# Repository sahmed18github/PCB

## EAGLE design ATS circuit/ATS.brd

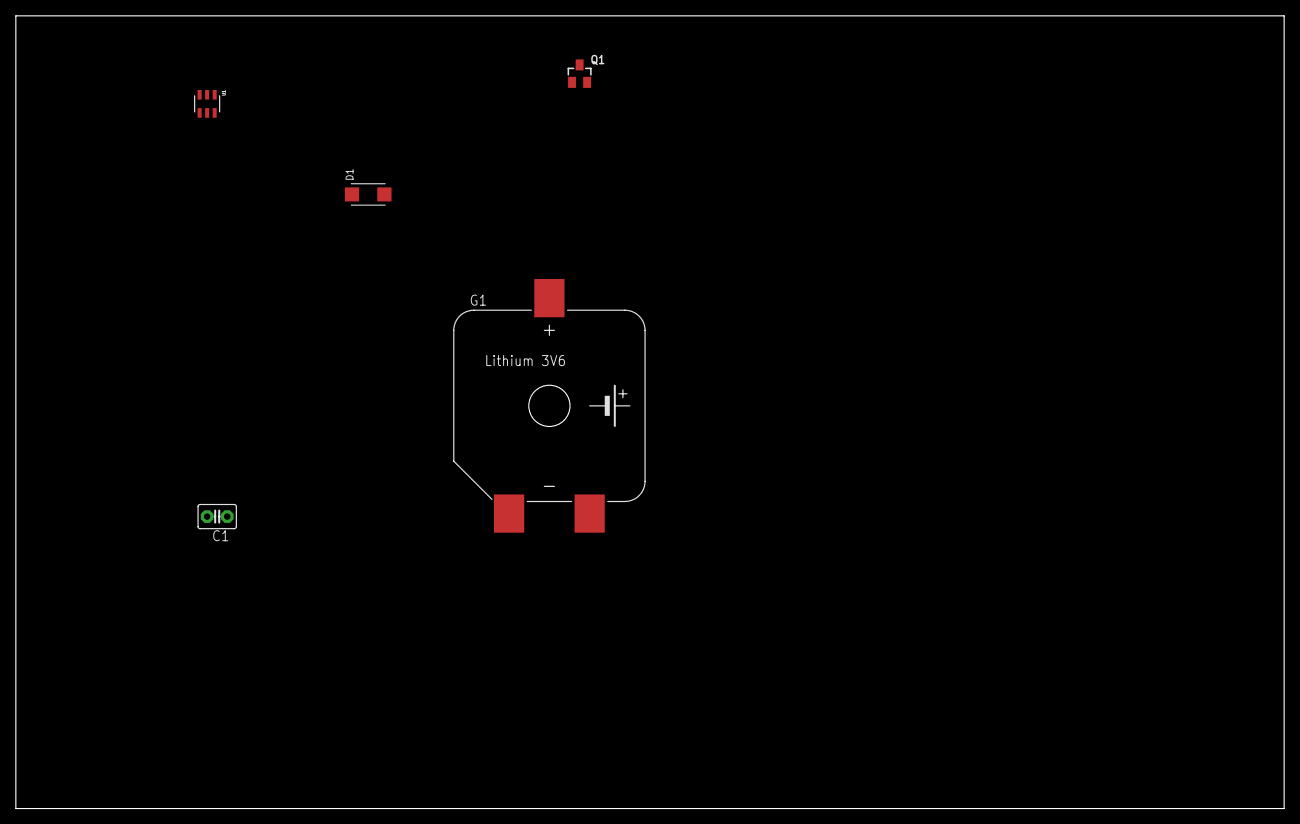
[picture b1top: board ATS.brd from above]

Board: 2 copper layers, 160.0 x 100.0 mm, 5 parts (0 on the bottom side), 4 nets, no tracks yet.

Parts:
C1: 22uF; C2.5-3
D1: SMD-DIODE-SCHOTTKY-40V-1A(DO-214AC); DO-214AC
G1: SL-340/SM3.6V
Q1: FDN306P; SSOT-3
U1: LTC4412ES6; TSOT-23_S6

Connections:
GND: C1.2, G1.-, U1.2, U1.3
unnamed: Q1.1, U1.5
unnamed: G1.+, Q1.2, U1.1
VCC: C1.1, D1.1, D1.2, Q1.3, U1.4, U1.6

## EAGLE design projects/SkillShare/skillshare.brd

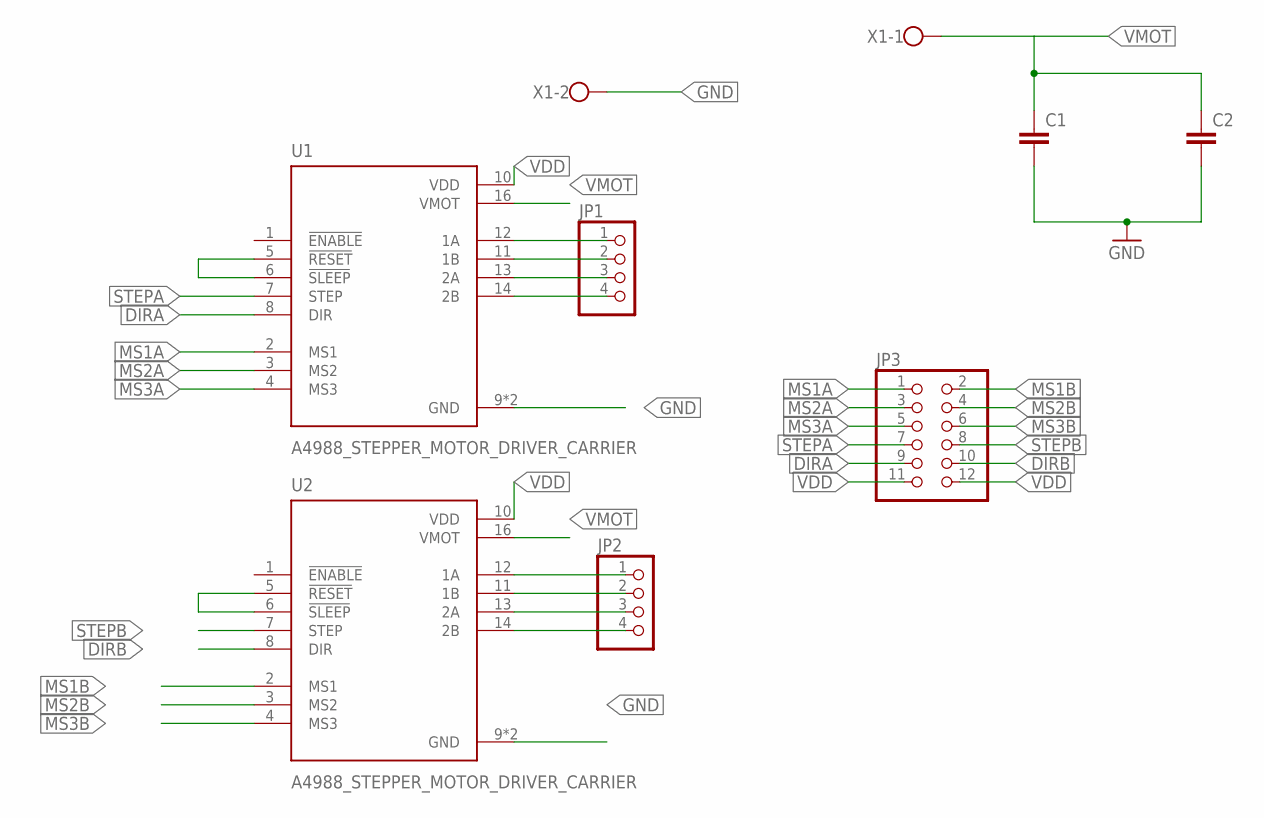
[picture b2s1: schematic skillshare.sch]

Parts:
C1, C2: C-EU025-025X050; C025-025X050
JP1, JP2: PINHD-1X4; 1X04
JP3: PINHD-2X6; 2X06
U1, U2: A4988_STEPPER_MOTOR_DRIVER_CARRIER; MODULE_A4988_STEPPER_MOTOR_DRIVER_CARRIER
X1: W237-102

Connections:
DIRA: JP3.9, U1.8 (DIR)
DIRB: JP3.10, U2.8 (DIR)
GND: C1.2, C2.2, U1.9 (GND), U1.15 (GND), U2.9 (GND), U2.15 (GND), X1.2
MS1A: JP3.1, U1.2 (MS1)
MS1B: JP3.2, U2.2 (MS1)
MS2A: JP3.3, U1.3 (MS2)
MS2B: JP3.4, U2.3 (MS2)
MS3A: JP3.5, U1.4 (MS3)
MS3B: JP3.6, U2.4 (MS3)
unnamed: JP1.1, U1.12 (1A)
unnamed: JP1.2, U1.11 (1B)
unnamed: JP1.3, U1.13 (2A)
unnamed: JP1.4, U1.14 (2B)
unnamed: JP2.1, U2.12 (1A)
unnamed: JP2.2, U2.11 (1B)
unnamed: JP2.3, U2.13 (2A)
unnamed: JP2.4, U2.14 (2B)
unnamed: U2.5 (!RESET), U2.6 (!SLEEP)
unnamed: U1.5 (!RESET), U1.6 (!SLEEP)
STEPA: JP3.7, U1.7 (STEP)
STEPB: JP3.8, U2.7 (STEP)
VDD: JP3.11, JP3.12, U1.10 (VDD), U2.10 (VDD)
VMOT: C1.1, C2.1, U1.16 (VMOT), U2.16 (VMOT), X1.1

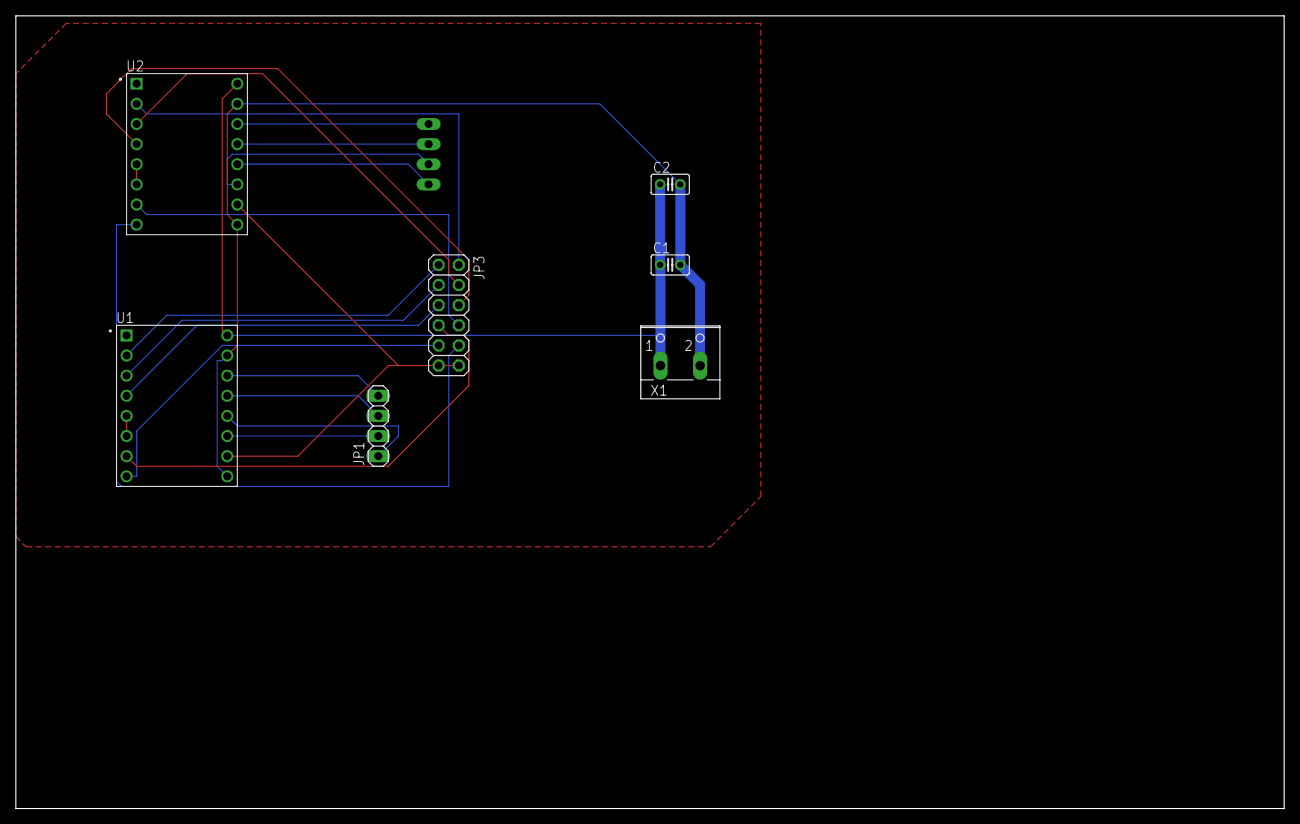
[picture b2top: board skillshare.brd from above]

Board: 2 copper layers, 160.0 x 100.0 mm, 8 parts (1 on the bottom side), 23 nets.

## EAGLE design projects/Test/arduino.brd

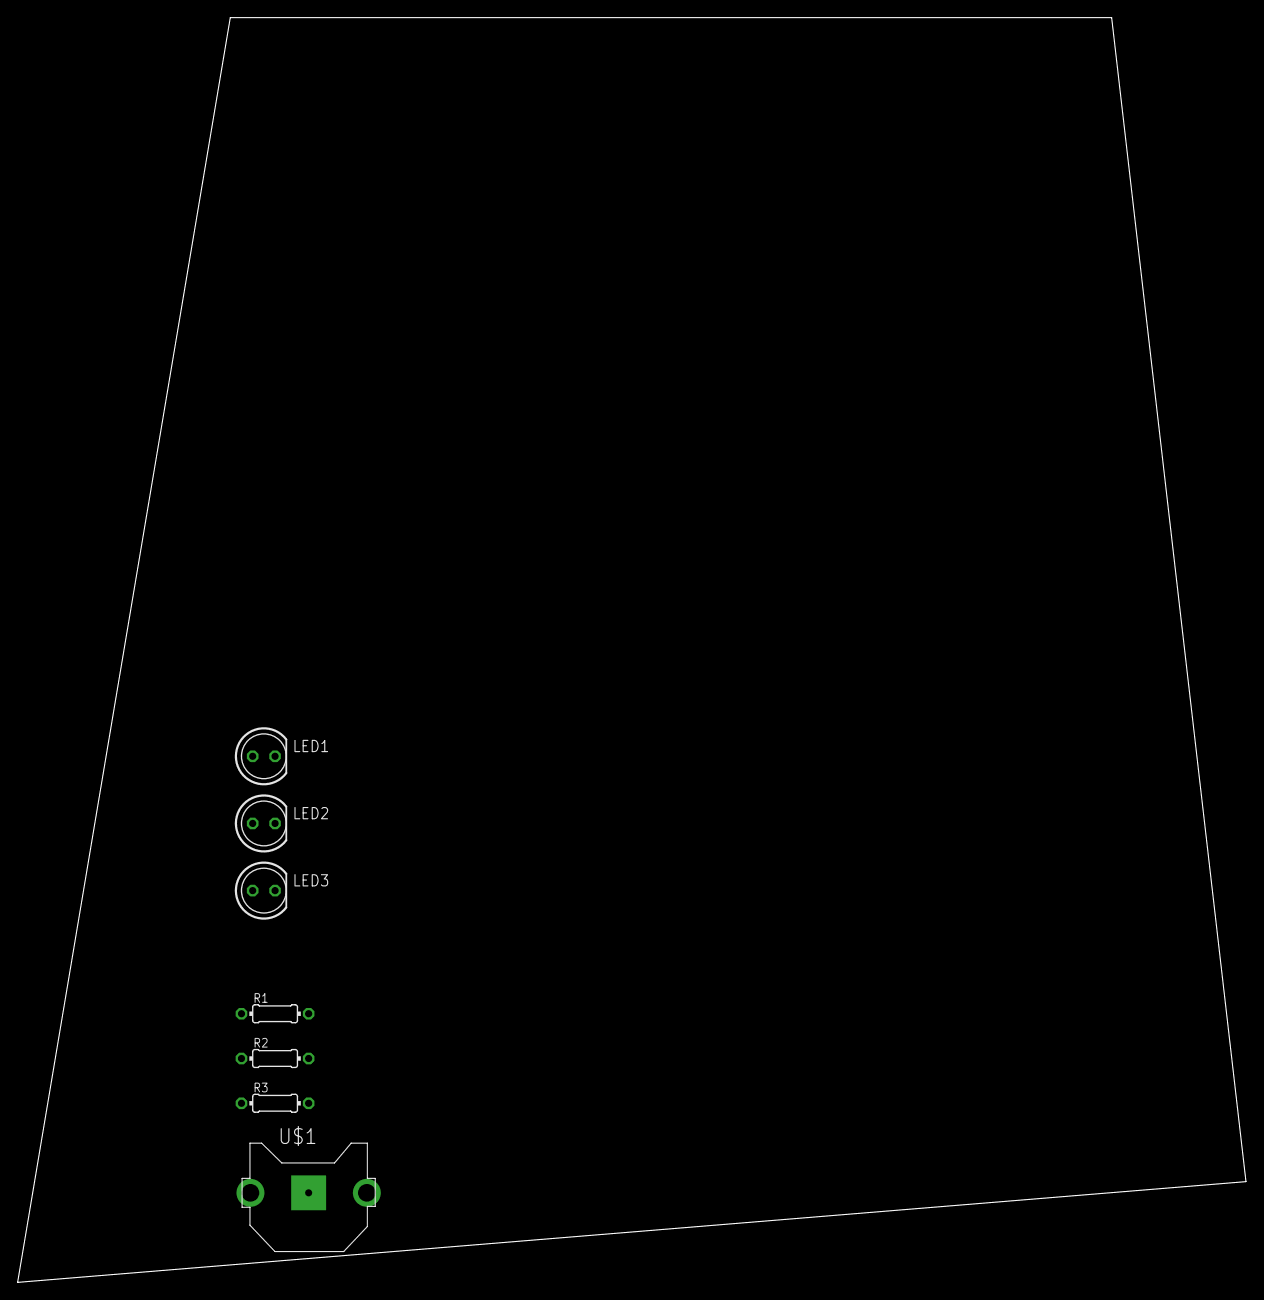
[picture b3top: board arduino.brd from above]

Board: 2 copper layers, 139.4 x 143.5 mm, 7 parts (0 on the bottom side), 5 nets, no tracks yet.

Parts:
LED1: BLUE; LED5MM
LED2: RED; LED5MM
LED3: GREEN; LED5MM
R1, R2, R3: 220E; 0204/7
U$1: CR1220-THM

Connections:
unnamed: LED3.K, R3.1
unnamed: LED2.K, R2.1
unnamed: LED1.K, R1.1
unnamed: LED1.A, LED2.A, LED3.A, U$1.+1, U$1.+2
unnamed: R1.2, R2.2, R3.2, U$1.-
